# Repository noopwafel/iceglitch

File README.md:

# iceGLITCH

iceGLITCH is a cheap, fun and terrible voltage glitcher!

You can use it to inject faults in the voltage line of targets, making them do weird things.

You can control both the normal and glitch voltage levels, and if you squint and sort of wave your hands a lot, then you can pretend you get ~200ps of resolution for the glitch length (time that the voltage is changed from normal to glitch level). Accuracy, on the other hand, is left as an exercise for the reader..

Many people played with this at the 'Hardware Slackers' assembly at 36C3! We're still recovering and will update the repository once we've gotten a few days of good sleep.

This is what a typical setup looks like:

And this is an example of what a real-world attack looks like (from our 36C3 assembly):

# Hardware

You can solder a good-enough (fun!) version of this glitcher using protoboard,
but nowadays we use a PCB version (see the 'pcb' directory). You can solder several
different combinations of components to get different glitcher designs, some of which make more
sense than others; however, we guarantee that all combinations will be both terrible and fun.

You can use it with any ICE40HX FPGA board with a PMOD connector; we're using the cheap (~22eur) 'iCEstick'.

Also it turns out you don't have to solder it nicely, it'll work fine anyway:

# Code

The 'TOE' directory contains code for some example targets.

The FPGA code (to be built using the open source yosys/nextpnr toolchain) is in the 'fpga' directory. We can't write verilog, there are no test cases, it is all terrible. We are sorry, our code is bad and we should feel bad. But it works :D

The (python) scripts are in the 'scripts' directory, including scripts to attack the example targets.

## History/Context

We built a horrible, horrible 5eur "oscilloscope" for our 35C3 side channel analysis workshop:
the [HorrorScope](https://github.com/albert-spruyt/HorrorScope).
This glitcher is our attempt to build a similar cheap-and-cheerful workshop platform for voltage glitching.

Some of our friends used it at the HITB CyberWeek in [October 2019](https://twitter.com/AllOurFaults/status/1184734015699464192), and we "released" it at 36C3 in December 2019.

Thanks to everyone who helped inspire or test our hacks, and thanks to @nedos in particular for making us realize we could
just use a cheap analog switch rather than overcomplicating things!

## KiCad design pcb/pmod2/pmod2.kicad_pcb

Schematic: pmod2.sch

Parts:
C1, C2, C3, C4, C5, C6, C7, C8, C9, C10, C11, C12, C13: C; C_0805_2012Metric_Pad1.15x1.40mm_HandSolder
J1: USB_B_Micro; USB_Micro-B_Amphenol_hax
J2: PMOD; PinHeader_2x06_P2.54mm_Vertical
J3, J4, J6, J7: Conn_01x04; PinHeader_1x06_P2.54mm_Vertical
J5: Conn_01x04; PinHeader_1x05_P2.54mm_Vertical
L1, L2: L; L_1210_3225Metric_Pad1.42x2.65mm_HandSolder
L3: Ferrite_Bead_Small; L_0805_2012Metric_Pad1.15x1.40mm_HandSolder
R1, R2, R3, R4, R5, R7: R; R_0805_2012Metric_Pad1.15x1.40mm_HandSolder
Rfb1, Rfb2, Rfb3, Rfb4: 0; R_0805_2012Metric_Pad1.15x1.40mm_HandSolder
Rld1, Rld2: R; R_0805_2012Metric_Pad1.15x1.40mm_HandSolder
U1: L272M; DIP-8_W7.62mm_LongPads
U2: MAX4619; DIP-16_W7.62mm_LongPads
U3: MCP4822; SOIC-8_3.9x4.9mm_P1.27mm
U4: TS5A63157; SOT-23-6
U5, U6: trigger; SOT-23-6
U7: MAX4232; SOT-23-8
U8: AP2210N-4.0; TSOT-23
U9: THS4631DDA; SOIC-8_3.9x4.9mm_P1.27mm

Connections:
+3V3: J2.6, J2.12, J7.1, J7.2, U5.5, U6.5
+5V: C6.2, C8.2, C9.2, C10.2, C11.2, C12.2, C13.2, J3.6, U1.2, U2.16, U3.1 (Vdd), U4.5, U7.8, U8.2, U9.7
/AMPFB1: Rfb1.2, Rfb3.1, U1.8, U7.2
/AMPFB2: Rfb2.2, Rfb4.2, U1.5, U7.6
/AMPOUT1: Rfb1.1, Rld1.1, U1.1, U2.2, U2.5, U2.12, U4.3, U7.1
/AMPOUT2: Rfb2.1, Rld2.2, U1.3, U2.1, U2.3, U2.13, U4.1, U7.7
/BUF1_IN: J7.3, U5.2
/BUF1_OUT: J7.4, U5.4
/BUF2_IN: J7.5, U6.2
/BUF2_OUT: J7.6, U6.4
/GPIO1: J2.3, J6.1
/GPIO2: J2.4, J6.2
/GPIO3: J2.7, J6.3
/POWER_OUT: J3.3, J3.4, U9.2, U9.6
/POWER_PREOUT: U2.4, U2.14, U2.15, U4.4, U9.3
/PWM_FILT1: C3.1, R4.1, U1.7, U3.6 (VB), U7.3
/PWM_FILT2: C5.1, R5.1, U1.6, U3.8 (VA), U7.5
/PWM_IN1: J2.9, J5.3, L1.2, U3.3 (SCK)
/PWM_IN2: J2.10, J5.2, L2.2, U3.2 (~CS)
/SDI_IN: J2.8, J5.4, J6.4, U3.4 (SDI)
/SWITCH_IN: J2.2, J5.1, R7.2, U2.9, U2.10, U2.11, U4.6
/TRIGGER_OUT: J2.1, J4.1, J4.2, J4.3, R3.2
GND: C1.1, C2.2, C3.2, C4.2, C5.2, C6.1, C7.1, C8.1, C9.1, C10.1, C11.1, C12.1, C13.1, J1.5, J2.5, J2.11, J3.1, J3.2, J3.5, J4.4, J4.5, J4.6, J5.5, J6.5, J6.6, R3.1, R7.1, Rfb3.2, Rfb4.1, Rld1.2, Rld2.1, U1.4, U2.6, U2.8, U3.5 (~LDAC), U3.7 (Vss), U4.2, U5.3, U6.3, U7.4, U8.1, U9.4
unnamed: C1.2, J1.1, L3.2
unnamed: C2.1, R1.1, R4.2
unnamed: C4.1, R2.1, R5.2
unnamed: C7.2, L3.1, U8.3
unnamed: L1.1, R1.2
unnamed: L2.1, R2.2

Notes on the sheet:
PWM filter/caps
pre-switch opamp
debug/extras
interface

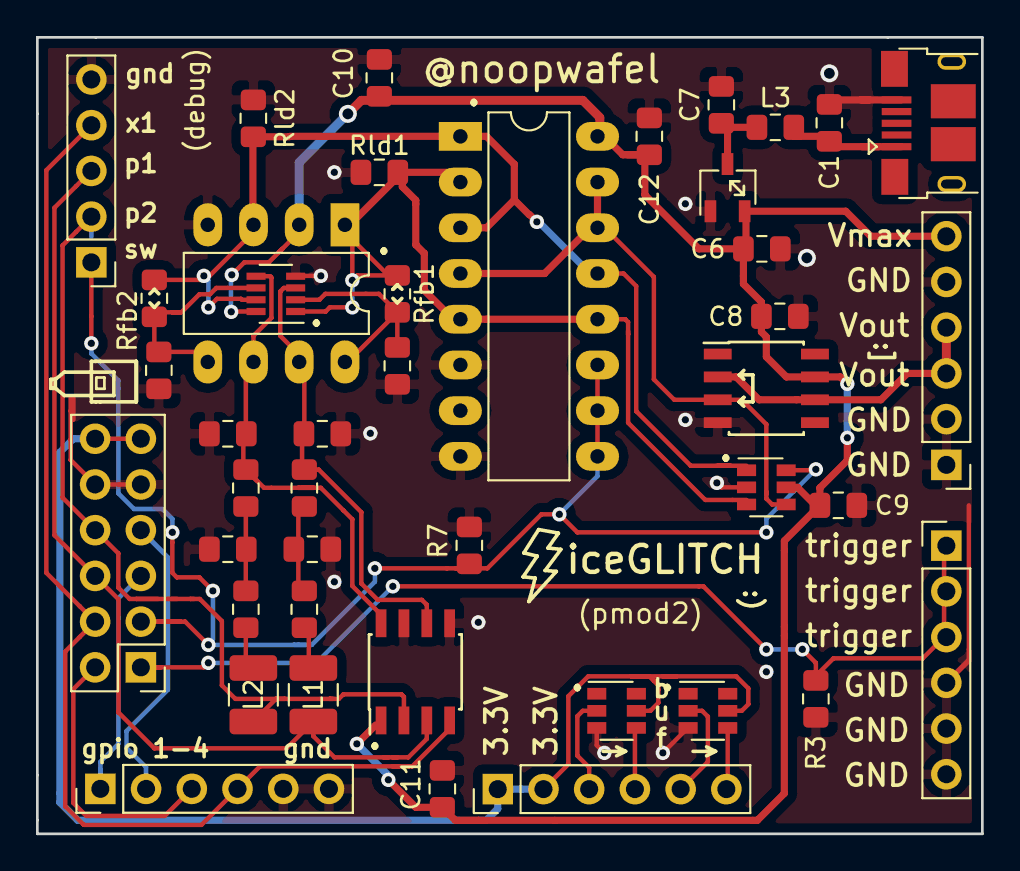
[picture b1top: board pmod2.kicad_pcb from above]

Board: 2 copper layers, 52.5 x 44.2 mm, 44 parts (1 on the bottom side), 29 nets.

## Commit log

2019-12-27 add pmod2 pcb
2019-12-27 add README, images
2019-12-27 add the verilog code
2019-12-27 add arduino-nano TOE source
2019-12-27 oops, this version only does high-resolution glitch length
2019-12-27 hedge bets some more
2019-12-27 add PCB image
2019-12-27 add scripts
